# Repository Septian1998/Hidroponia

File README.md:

# Hidroponia
Project of Hydroponics control

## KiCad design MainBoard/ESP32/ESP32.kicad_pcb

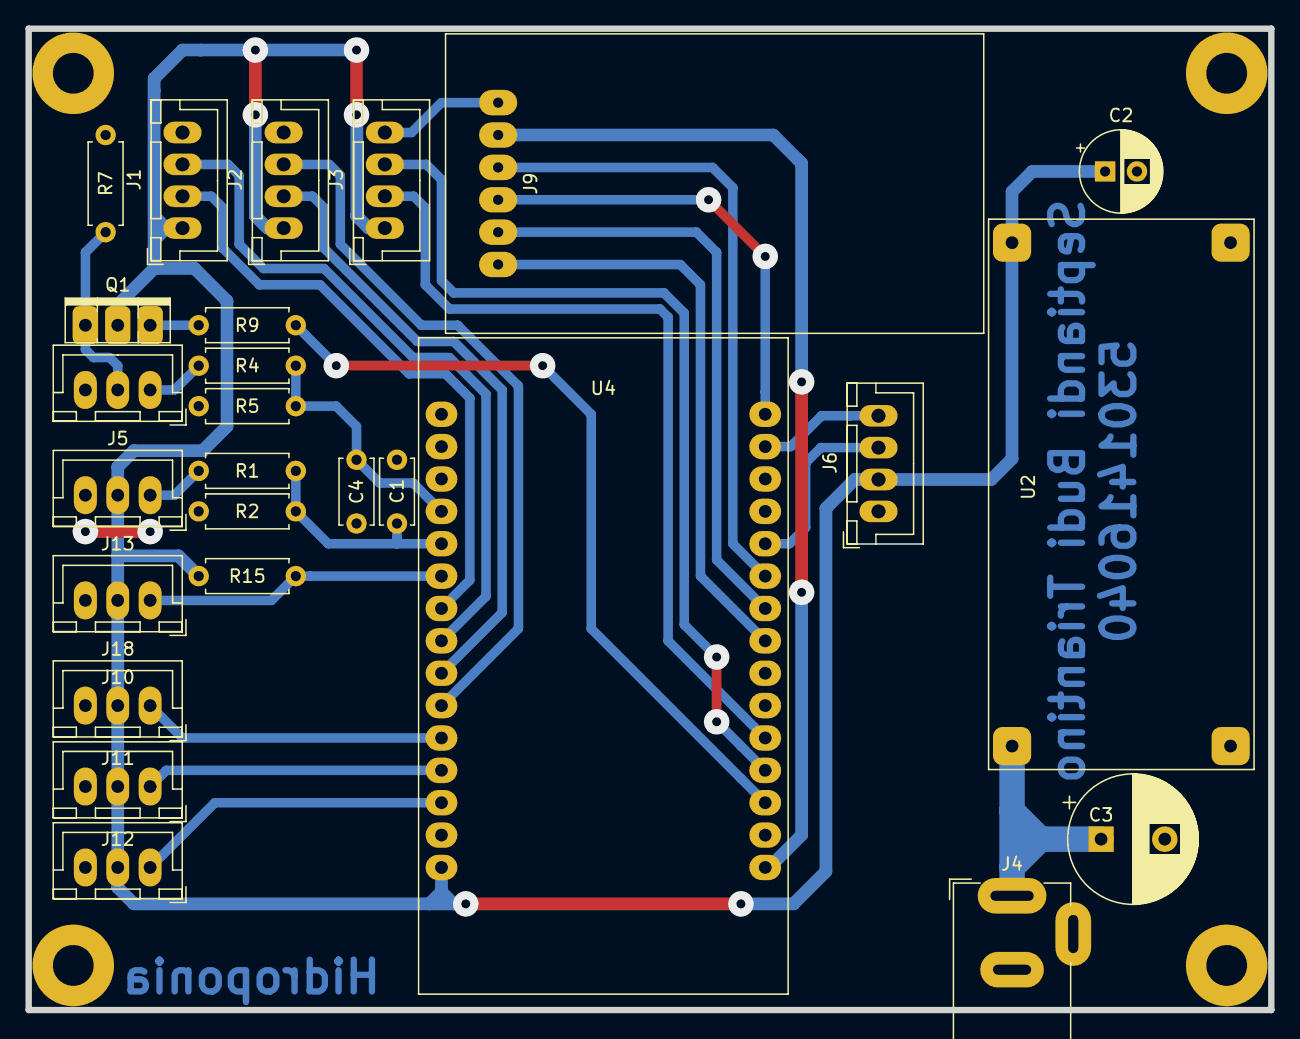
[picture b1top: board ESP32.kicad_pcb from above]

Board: 2 copper layers, 97.5 x 77.0 mm, 30 parts (0 on the bottom side), 27 nets.

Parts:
C1, C4: 104; C_Disc_D5.0mm_W2.5mm_P5.00mm
C2: 47uf; CP_Radial_D6.3mm_P2.50mm
C3: 1000u; CP_Radial_D10.0mm_P5.00mm
H1, H2, H3, H4: Mounting; MountingHole_3.2mm_M3_Pad
J1: A MIX; JST_XH_B4B-XH-A_1x04_P2.50_DIY
J2: B MIX; JST_XH_B4B-XH-A_1x04_P2.50_DIY
J3: pH; JST_XH_B4B-XH-A_1x04_P2.50_DIY
J4: Power Supply; BarrelJack_Wuerth_6941xx301002
J5, J13: pH_SNS; JST_XH_B3B-XH-A_1X03_P2.50mm_DIY
J6: I2C_1; JST_XH_B4B-XH-A_1x04_P2.50_DIY
J9: SD_CARD_Module; SD_Card
J10: OUT1; JST_XH_B3B-XH-A_1X03_P2.50mm_DIY
J11: OUT2; JST_XH_B3B-XH-A_1X03_P2.50mm_DIY
J12: OUT3; JST_XH_B3B-XH-A_1X03_P2.50mm_DIY
J18: Temp_SNS; JST_XH_B3B-XH-A_1X03_P2.50mm_DIY
Q1: BD139; TO-126-3_DIY
R1, R4: 5k1; R_Axial_DIN0207_L6.3mm_D2.5mm_P7.62mm_Horizontal
R2, R5, R7: 10k; R_Axial_DIN0207_L6.3mm_D2.5mm_P7.62mm_Horizontal
R9: 200; R_Axial_DIN0207_L6.3mm_D2.5mm_P7.62mm_Horizontal
R15: 4k7; R_Axial_DIN0207_L6.3mm_D2.5mm_P7.62mm_Horizontal
U2: LM2596
U4: ESP32-DevKit_V1

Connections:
+3V3: J9.5, U4.16
+5V: C2.1, J1.1, J2.1, J3.1, J6.2, J10.2, J11.2, J12.2, J13.2, J18.2, Q1.2, R15.2, U2.3, U4.15
+12V: C3.1, J4.1, U2.1
/A_ECHO: J1.3, U4.8
/A_TRIG: J1.2, U4.7
/B_ECHO: J2.3, U4.10
/B_TRIG: J2.2, U4.9
/CLK\SCK: J9.2, U4.24
/CMD\MOSI: J9.3, U4.30
/DAT0\MISO: J9.4, U4.25
/DAT3\CS: J9.1, U4.23
/OUT1: J10.1, U4.11
/OUT2: J11.1, U4.12
/OUT3: J12.1, U4.13
/SCL: J6.4, U4.29
/SDA: J6.3, U4.26
/TDS_SNS: C4.1, R4.2, R5.1, U4.4
/TD_SW: R9.1, U4.18
/TEMP_SNS: J18.1, R15.1, U4.6
/pH_ECHO: J3.3, U4.19
/pH_SNS: C1.1, R1.2, R2.1, U4.5
/pH_TRIG: J3.2, U4.20
GND: C1.2, C2.2, C3.2, C4.2, J1.4, J2.4, J3.4, J4.2, J4.3, J5.3, J6.1, J9.6, J10.3, J11.3, J12.3, J13.3, J18.3, R2.2, R5.2, R7.2, U2.2, U2.4, U4.14, U4.17
unnamed: J5.1, R4.1
unnamed: J5.2, Q1.1, R7.1
unnamed: J13.1, R1.1
unnamed: Q1.3, R9.2

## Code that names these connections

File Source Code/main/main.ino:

//library untuk SD Card
#include "FS.h"
#include "SD.h"
#include <SPI.h>

//library untuk I2C sensor
//#include <Wire.h>

//library untuk DS18b20
//#include <OneWire.h>
//#include <DallasTemperature.h>

//library untuk dapatkan waktu dari NTP Server dan GET
#include <WiFi.h>
#include <NTPClient.h>
#include <WiFiUdp.h>
#include <HTTPClient.h>

//library untuk LCD_I2C
#include <LiquidCrystal_I2C.h>

//library untuk Servo
#include <Servo_ESP32.h>

#define pH_sns 35
#define TDS_sns 34
#define TDS_sw 15
//#define temp_sns 32

#define ssid "Halopro"/*"Bang Bud"*/
#define pass "2021proto"/*"septian19"*/
#define SD_CS 5

//Pin Ultrasonic
#define A_TRIG 33
#define A_ECHO 25
#define B_TRIG 26
#define B_ECHO 27
#define pH_TRIG 4
#define pH_ECHO 2

//#define MAX_DISTANCE 400

#define Amix 0  //Amix
#define Bmix 2  //bmix
#define pHup 1  //pHup

//variable pH
float pHValue;
uint16_t valpH[10];
float avgpH, jumlahpH;
float ph_sp= 6;
float ph_error_1, ph_er=0, ph_dError;
float ph_def;

//variable TDS
float TDSValue;
//uint16_t valTDS[10];
//float avgTDS, jumlahTDS;
//float tds_sp= 1175;
//float tds_error_1, tds_er=0, tds_dError;
//float tds_def;

TaskHandle_t TaskFLC;

String address = "http://hidroponia-app.herokuapp.com/api/";

unsigned long lastTime = 0;
unsigned long timerDelay = 60000; //60 detik
unsigned long lastTimeLCD = 0;
unsigned long timerDelayLCD = 1000; //1 detik

//variable suhu
int suhu;

LiquidCrystal_I2C lcd(0x27, 20, 4);

//Menyimpan pembacaan angka di RTC memory
RTC_DATA_ATTR int readingID = 0;

String dataMessage;

//definisikan NTP Client untuk mendapatkan waktu
WiFiUDP ntpUDP;
NTPClient timeClient(ntpUDP);

//definisikan servo
Servo /*A_MIX, B_MIX,*/ pH_servo;
//float def;

//Variebel untuk menyimpan tanggal dan waktu
String formatedDate;
String dayStamp;
String timeStamp;

byte derajat[] = {0x06, 0x09, 0x09, 0x06, 0x00, 0x00, 0x00, 0x00};

float Sensor[3];
int tank[3];
int place;

void setup()
{
    //Wire.begin();
    Serial.begin(115200);
    xTaskCreatePinnedToCore(FLC, "TaskFLC", 10000, NULL, 1, &TaskFLC, 0);
    //A_MIX.attach(13);
    //B_MIX.attach(14);
    pH_servo.attach(12);
    pinMode(A_TRIG,OUTPUT);
    pinMode(A_ECHO,INPUT);
    pinMode(B_TRIG,OUTPUT);
    pinMode(B_ECHO,INPUT);
    pinMode(pH_TRIG,OUTPUT);
    pinMode(pH_ECHO,INPUT);
    lcd.begin();
    lcd.backlight();
    lcd.createChar(0, derajat);
    //konek ke Wi-Fi network dengan SSID dan password
    //Serial.print("Connecting to ");
    //Serial.println(ssid);
    WiFi.begin(ssid, pass);
    /*while (WiFi.status() != WL_CONNECTED)
    {
        delay(500);
        Serial.print(".");
    }
    Serial.println(" ");
    Serial.println("WiFi Connected");*/

    //inisialisasi NTPClient untuk mendapatka waktu
    timeClient.begin();
    timeClient.setTimeOffset(25200);

    //inisialisasi SD Card
    SD.begin(SD_CS);
    if(!SD.begin(SD_CS))
    {
        Serial.println("Card Mount Failed");
        return;
    }
    uint8_t cardType = SD.cardType();
    if(cardType == CARD_NONE)
    {
        Serial.println("No SD card attached");
        return;
    }
    //Serial.println("Initializing SD card . . .");
    if(!SD.begin(SD_CS))
    {
        Serial.println("ERROR - SD card Initialization failed!");
        return;
    }
    //jika file data.txt tidak ada
    //buat file di SD card dan tulisdata label
    File file = SD.open("/data.txt");
    if(!file)
    {
        Serial.println("File doens't exist");
        Serial.println("Creating file...");
        writeFile(SD, "/data.txt", "Reading ID, Date, Hour, pH up Tank, pH \r\n");
    }
    else 
    {
        Serial.println("File already exists");  
    }
    file.close();


}

void FLC(void * pvParameters)
{
    for(;;)
    {
        //Baca Sensor
        get_pH();
        
        ph_er = ph_sp - pHValue;
        
        //tds_error_1 = tds_er;
        //tds_er = tds_sp - TDSValue;
        //tds_dError = tds_er - tds_error_1;

        if(ph_er!=0/*ph_er>=0.5 && ph_er<=(-0.5)*/)
        {
            get_pH();
            
            ph_error_1 = ph_er;
            ph_er = ph_sp - pHValue;
            ph_dError = ph_er - ph_error_1;

            ph_def = fuzzy(ph_er, ph_dError);
            Serial.println(round(ph_def));
            pH_servo.write(round(ph_def));
        }
        else if(ph_er==0/*ph_er<=0.5 && ph_er>=(-0.5)*/)
        {
            for(int dly=0; dly<=180; dly++)
            {   
                pH_servo.write(0);
                delay(1000);
            }
        }
        
        /*float sp= 4.9;
        float error_1, er=0, dError;
        float def;
        getReadings();
        error_1 = er;
        er = sp - pHValue;
        dError = er - error_1;
        Serial.println("error: " + String(er));
        Serial.println("derror: " + String(dError));
        def = fuzzy(er, dError);
        Serial.println(round(def));
        A_MIX.write(round(def));*/
    }
}

void loop()
{   
    getReadings();
    get_pH();
    if((millis() - lastTimeLCD) > timerDelayLCD)
    {
        getTimeStamp();
        LCD_Display();
        lastTimeLCD = millis();
    }
    if((millis() - lastTime) > timerDelay)
    {
        //sendGET();
        logSDCard();
        readingID++;
        lastTime = millis();
    }
}

// Write to the SD card (DON'T MODIFY THIS FUNCTION)
void writeFile(fs::FS &fs, const char * path, const char * message) 
{
    Serial.printf("Writing file: %s\n", path);

    File file = fs.open(path, FILE_WRITE);
    if(!file)  
    {
        Serial.println("Failed to open file for writing");
        return;
    }
    if(file.print(message)) 
    {
        Serial.println("File written");
    } 
    else 
    {
        Serial.println("Write failed");
    }
    file.close();
}

// Append data to the SD card (DON'T MODIFY THIS FUNCTION)
void appendFile(fs::FS &fs, const char * path, const char * message) 
{
    Serial.printf("Appending to file: %s\n", path);

    File file = fs.open(path, FILE_APPEND);
    if(!file) 
    {
        Serial.println("Failed to open file for appending");
        return;
    }
    if(file.print(message))
    {
        Serial.println("Message appended");
    }
    else
    {
        Serial.println("Append failed");
    }
    file.close();
}

void get_pH()
{
    //baca sensor pH
    for (int a = 0; a < 10; a++)
    {
        valpH[a] = analogRead(pH_sns);
        delay(30);
    }
    jumlahpH = 0;
    for (int b = 0; b < 10; b++)
    {
        jumlahpH += valpH[b];
    }
    avgpH = (jumlahpH / 10) * 3.3 / 4095 ;
    pHValue = 3.5*avgpH;
    //pHValue = -0.0092 * avgpH  + 28.078; //-0.0092 adalah gradien dan 28.078 adalah koefisien kalibrasi
    //Serial.println(pHValue);
}

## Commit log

2020-10-17 Add Test_LCD
2020-10-18 Add Main Board
2020-10-21 Add Servo test
2020-10-28 Add Test GET
2020-10-30 Fix Test_GET.ino
2020-10-30 Change Field Value
2020-10-31 Add main.ino
2020-10-31 Add Test_ADC.ino
2020-11-03 Add Test_SD.ino
2020-11-06 Test main.ino
2020-11-07 Add Test_fuzzy.ino
2020-11-17 Fix Test_fuzzy.ino
2020-11-18 Fix Error main.ino
2020-11-18 Add LCD_Display.ino
2020-11-22 Change FLC argoritm
2020-11-25 Fix program
2020-11-29 Fix Main Board
2020-12-18 Fix display
2021-01-01 Upload from Laptop
2021-01-16 Add files from PC
2021-04-28 Update Main Board
2021-04-28 Update Source Code
2021-04-28 Add 3D Visual
2021-05-16 Add fix calculation
2021-05-16 fix conversion
